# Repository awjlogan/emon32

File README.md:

# Energy Monitor 32

## Introduction

_Energy Monitor 32_ (emon32) is a system for measuring power consumption using _current transfomers_ (CTs). It is based heavily on the work done by [OpenEnergyMonitor](https://openenergymonitor.org), particularly the [emonTx](https://github.com/openenergymonitor/emontx4). It is designed to be compatible with the downstream data requirements of that system.

The emonTx energy monitors are currently based around the ATMega328, as made popular by Arduino, and an extended version, the AVR128DB. These chips are expensive, have few peripherals, and are being pushed to the limit of their data processing capability. The aims of this project are:

- Provide a low cost, high performance energy monitoring system.
- Provide a scalable and modular system.
- Provide an architecture agnostic library to handle energy monitoring functions.

There is also [firmware available](https://github.com/awjlogan/emon32-fw) to enable a complete energy monitoring system.

## Getting started

There is currently one implementation:

- [emonPi3](pcb/emonpi3/README.md)

> [!NOTE]
> The emonPi3 will be available full assembled from the OpenEnergyMonitor shop in 2025/2026.

## Microcontroller Selection

The firmware is agnostic to the microcontroller used, although a modern 32 bit core is preferred. This implementation targets the [Microchip SAMD series](https://www.microchip.com/en-us/products/microcontrollers-and-microprocessors/32-bit-mcus/sam-32-bit-mcus/sam-d) - this allows easy porting from small and cheap (SAMD1x) to higher performance and capability microcontrollers, such as the SAMD2x and SAMD5x. The SAMD family has the following useful functions

- Differential ADC (dual channel for SAMD5x)
- Asynchronous event system
  - This allows precise sample timing without any interrupt overhead
- Generic serial communication modules
- Flexible clocking system
  - High speed clocks are available for the core, and separate clocks for each peripheral
  - Clocks and peripherals can be gated when not in use
- USB virtual serial port (SAMD21 and SAMD51 only)
- USB bootloader (SAMD11, SAMD21, SAMD51 only)

If you would like to use a different microcontroller, the following features are recommended:

- Minimum 24 MHz clock
- Timer with 1 us resolution
- DMA (minimum 2 channels)
- 2x UART module
- SPI module
- I2C module

Functions in the main loop are abstacted from the underlying hardware. Implementation specific configuration (for example, configuring the ADC) must be provided.

## License

This project is licensed under the [Creative Commons Attribution Sharealike 4.0](https://creativecommons.org/licenses/by-sa/4.0/deed.en). Any alterations must be made available immediately, or upon request.

## Acknowledgements

- [OpenEnergyMonitor](https://openenergymonitor.org)
- Rob Wall of Open Energy Monitor forums for lots of in depth discussion around sampling strategies.
- Rupert on OEM forums for PCB improvements.

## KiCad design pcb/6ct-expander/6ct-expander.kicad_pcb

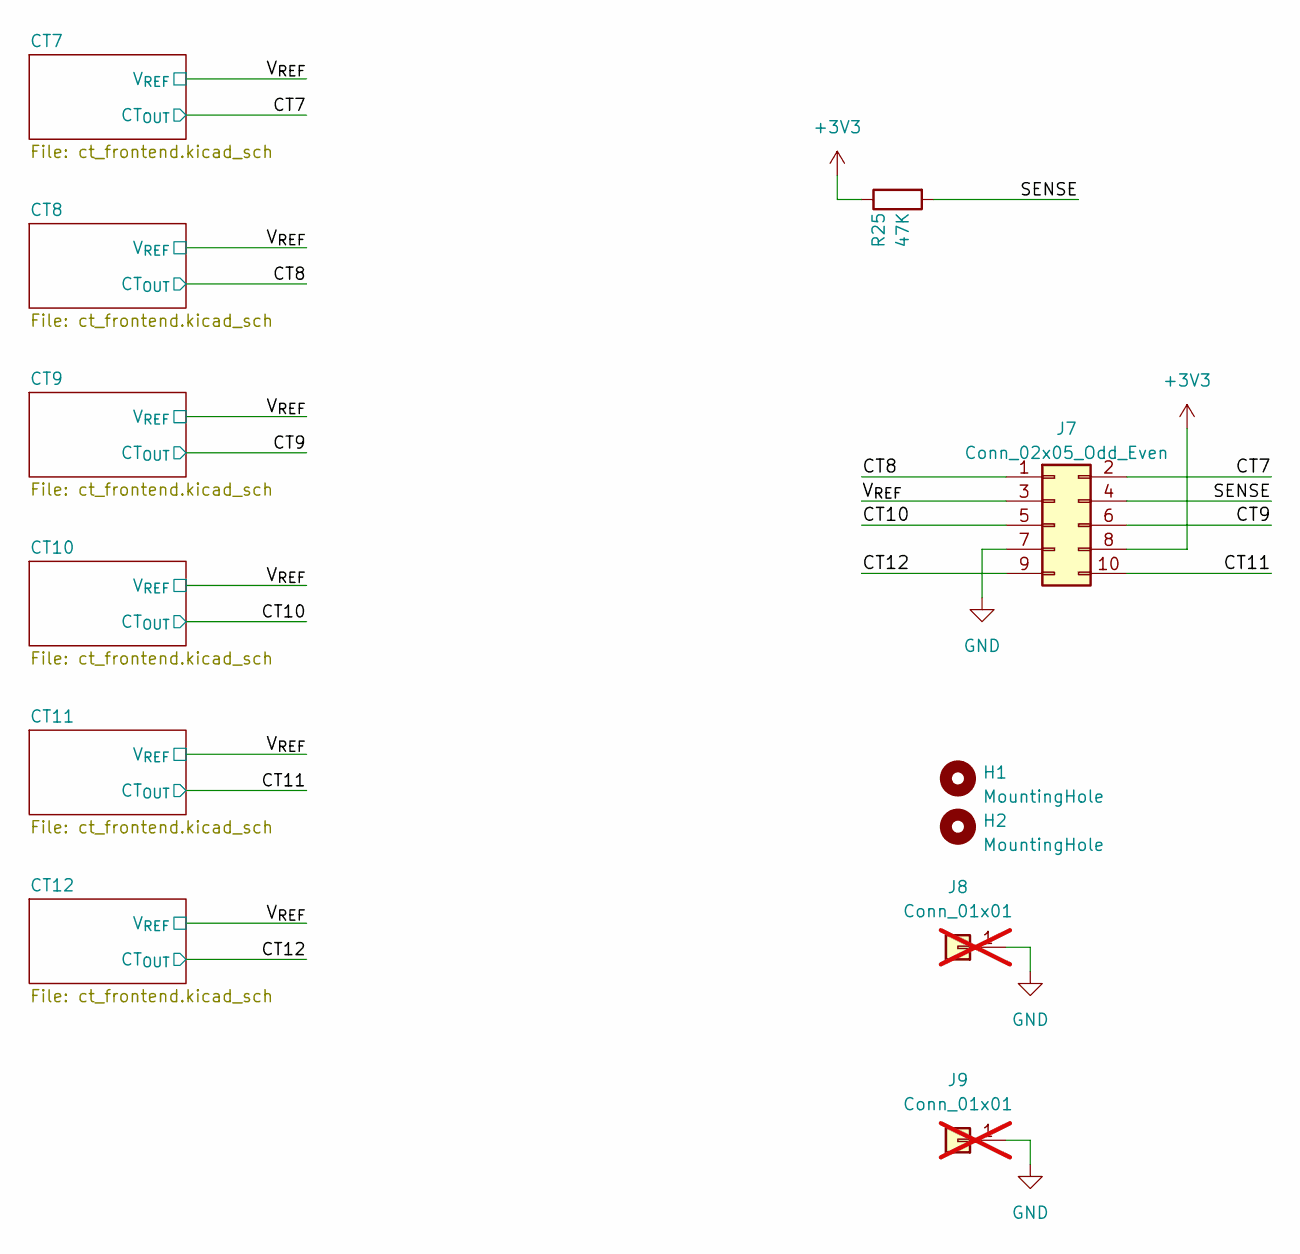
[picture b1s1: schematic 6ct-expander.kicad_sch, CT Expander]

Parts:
H1, H2: MountingHole; MountingHole_2.7mm_M2.5
J7: Conn_02x05_Odd_Even; PinHeader_2x05_P2.54mm_Vertical
J8, J9: Conn_01x01; PinHeader_1x01_P2.54mm_Vertical; not fitted
R25: 47K; R_0603_1608Metric; LCSC C23162

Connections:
+3V3: J7.8, R25.1
/CT7: J7.2; also elsewhere on the board
/CT8: J7.1; also elsewhere on the board
/CT9: J7.6; also elsewhere on the board
/CT10: J7.5; also elsewhere on the board
/CT11: J7.10; also elsewhere on the board
/CT12: J7.9; also elsewhere on the board
/SENSE: J7.4, R25.2
/V_{REF}: J7.3; also elsewhere on the board
GND: J7.7, J8.1, J9.1; also elsewhere on the board

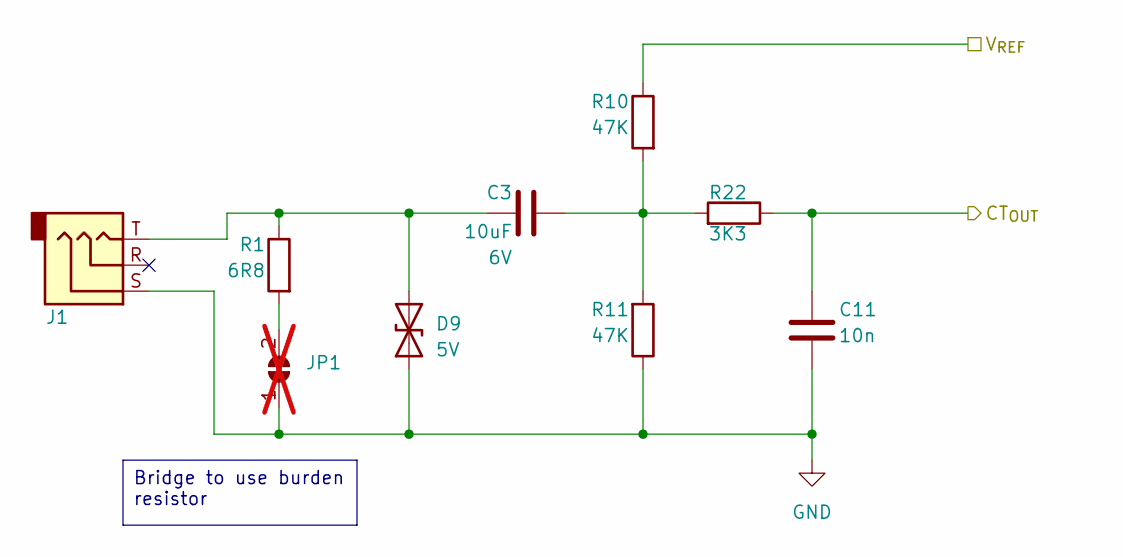
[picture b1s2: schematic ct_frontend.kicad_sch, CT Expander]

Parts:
C3: 10uF; C_0603_1608Metric; Voltage 6V; LCSC C19702
C11: 10n; C_0603_1608Metric; LCSC C57112
D9: 5V; D_SOD-523; MPN DF2B7AE,H3F; Mouser 757-DF2B7AEH3F
J1: SJ-3524-SMT-TR; Jack_3.5mm_CUI_SJ-3524-SMT_Horizontal; LCSC C4991872
JP1: SolderJumper_2_Open; SolderJumper-2_P1.3mm_Open_TrianglePad1.0x1.5mm; not fitted
R1: 6R8; R_1206_3216Metric; LCSC C2107438
R10, R11: 47K; R_0603_1608Metric; LCSC C23162
R22: 3K3; R_0603_1608Metric; LCSC C22978

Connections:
/CT7: C11.1, R22.1; also elsewhere on the board
/V_{REF}: R10.1; also elsewhere on the board
GND: C11.2, D9.1 (A1), J1.S, JP1.1 (A), R11.1; also elsewhere on the board
unnamed: C3.2, R10.2, R11.2, R22.2
unnamed: C3.1, D9.2 (A2), J1.T, R1.1
unnamed: JP1.2 (B), R1.2

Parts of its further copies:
C1, C4, C6, C8, C10: 10uF; C_0603_1608Metric; Voltage 6V; LCSC C19702
C2, C5, C7, C9, C12: 10n; C_0603_1608Metric; LCSC C57112
D1, D2, D3, D4, D5: 5V; D_SOD-523; MPN DF2B7AE,H3F; Mouser 757-DF2B7AEH3F
J2, J3, J4, J5, J6: SJ-3524-SMT-TR; Jack_3.5mm_CUI_SJ-3524-SMT_Horizontal; LCSC C4991872
JP2, JP3, JP4, JP5, JP6: SolderJumper_2_Open; SolderJumper-2_P1.3mm_Open_TrianglePad1.0x1.5mm; not fitted
R2, R6: 6R8; R_1206_3216Metric; LCSC C2107438
R3, R4, R7, R8, R13, R14, R17, R18, R21, R23: 47K; R_0603_1608Metric; LCSC C23162
R5, R9: 3K3; R_0603_1608Metric; LCSC C22978

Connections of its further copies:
/CT8: C2.1, R5.1; also elsewhere on the board
/CT9: C5.1, R9.1; also elsewhere on the board
/CT10: C7.1; also elsewhere on the board
/CT11: C9.1; also elsewhere on the board
/CT12: C12.1; also elsewhere on the board
/V_{REF}: R3.1, R7.1, R13.1, R17.1, R21.1; also elsewhere on the board
GND: C2.2, C5.2, C7.2, C9.2, C12.2, D1.1 (A1), D2.1 (A1), D3.1 (A1), D4.1 (A1), D5.1 (A1), J2.S, J3.S, J4.S, J5.S, J6.S, JP2.1 (A), JP3.1 (A), JP4.1 (A), JP5.1 (A), JP6.1 (A), R4.1, R8.1, R14.1, R18.1, R23.1; also elsewhere on the board
unnamed: C1.2, R3.2, R4.2, R5.2
unnamed: C4.2, R7.2, R8.2, R9.2
unnamed 13: C6.2, R13.2, R14.2; also elsewhere on the board
unnamed 14: C8.2, R17.2, R18.2; also elsewhere on the board
unnamed 15: C10.2, R21.2, R23.2; also elsewhere on the board
unnamed: C1.1, D1.2 (A2), J2.T, R2.1
unnamed: C4.1, D2.2 (A2), J3.T, R6.1
unnamed 18: C6.1, D3.2 (A2), J4.T; also elsewhere on the board
unnamed 19: C8.1, D4.2 (A2), J5.T; also elsewhere on the board
unnamed 20: C10.1, D5.2 (A2), J6.T; also elsewhere on the board
unnamed: JP2.2 (B), R2.2
unnamed: JP3.2 (B), R6.2
unnamed 25: JP4.2 (B); also elsewhere on the board
unnamed 26: JP5.2 (B); also elsewhere on the board
unnamed 27: JP6.2 (B); also elsewhere on the board

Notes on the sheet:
Bridge to use burden resistor

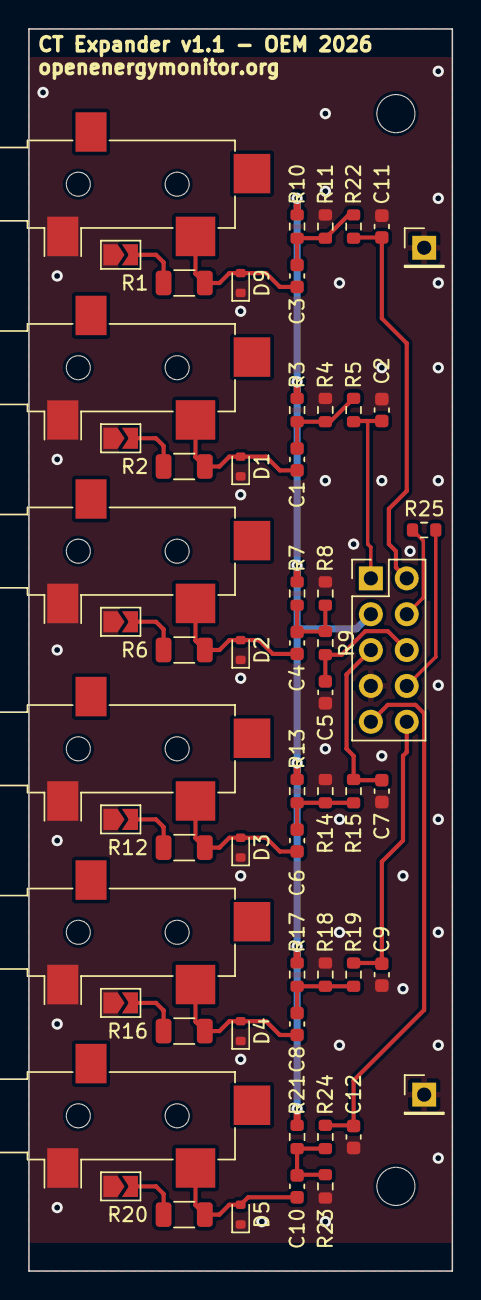
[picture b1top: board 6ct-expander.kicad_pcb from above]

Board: 2 copper layers, 30.0 x 88.0 mm, 60 parts (0 on the bottom side), 28 nets.

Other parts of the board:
R12, R16, R20: 6R8; R_1206_3216Metric
R15, R19, R24: 3K3; R_0603_1608Metric

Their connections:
/CT10: R15.1; also elsewhere on the board
/CT11: R19.1; also elsewhere on the board
/CT12: R24.1; also elsewhere on the board
unnamed 13: R15.2; also elsewhere on the board
unnamed 14: R19.2; also elsewhere on the board
unnamed 15: R24.2; also elsewhere on the board
unnamed 18: R12.1; also elsewhere on the board
unnamed 19: R16.1; also elsewhere on the board
unnamed 20: R20.1; also elsewhere on the board
unnamed 25: R12.2; also elsewhere on the board
unnamed 26: R16.2; also elsewhere on the board
unnamed 27: R20.2; also elsewhere on the board

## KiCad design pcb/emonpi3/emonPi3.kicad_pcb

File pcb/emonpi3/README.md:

# emonPi3

_emonPi3_ is a drop in replacement for the [emonPi2](https://docs.openenergymonitor.org/emonpi2/index.html). The main change is the use of a modern high performance microcontroller in place of the aging and expensive AVR parts. Additionally, the firmware moves away from using Arduino as the base environment.

## Firmware

Firmware for the emonPi3 is available [here](https://github.com/awjlogan/emon32-fw). The emonPi3 comes preloaded with a USB bootloader, allowing the firmware to be updated without any specialised hardware.

## Generating manufacturing outputs

You will need to have [KiCad 7](https://www.kicad.org/) installed. In the `emonpi3` folder, run `python3 generate.py`. This will make a folder called `output-<gitrev>` with the following contents:

  - KiCad schematic annotated with git revision
  - KiCad PCB annotated with git revision
  - Schematic PDF
  - Floorplan PDF
  - Bill of materials CSV
  - Gerbers output
  - 3D render (STEP format)

This has been tested on Linux and macOS.

## Changelog

### 1.0

Production

- Correct front panel LED footprint
- Routing tweaks

### 0.2

First production candidate

- Correct SPI connection
- Move LED to front panel
- ESD protection on all inputs and buttons
- Expose reset to Pi connection

### 0.1

First public limited manufacturing run.

- Add hardware zero crossing detector.
- Add ADC calibration hardware.
- Add more testpoints.
- Move EEPROM and reassign serial modules.
- Add user button, LEDs, and external I2C header.

### 0.1-dev

- First bring up of the emonPi3. 
  - Directly physically compatible with the existing emonPi2. 
- Change to 4-layer board
- Add extra filters and power protection

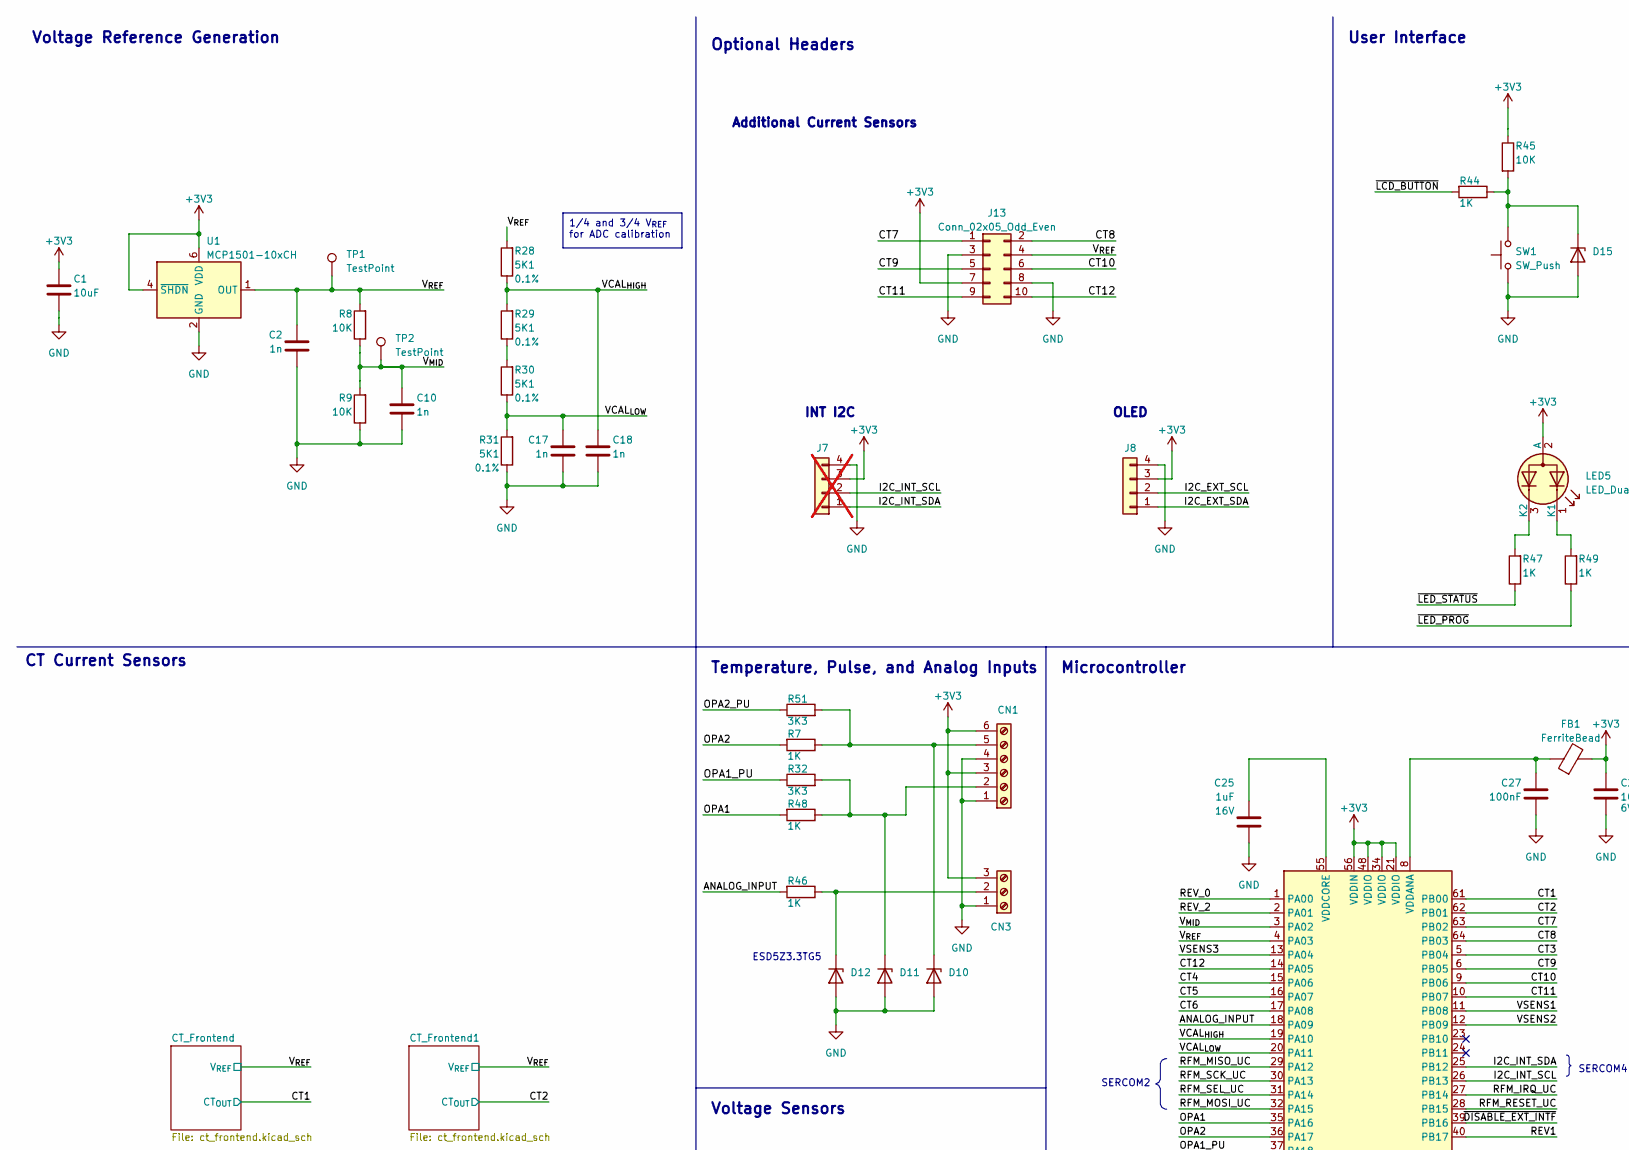
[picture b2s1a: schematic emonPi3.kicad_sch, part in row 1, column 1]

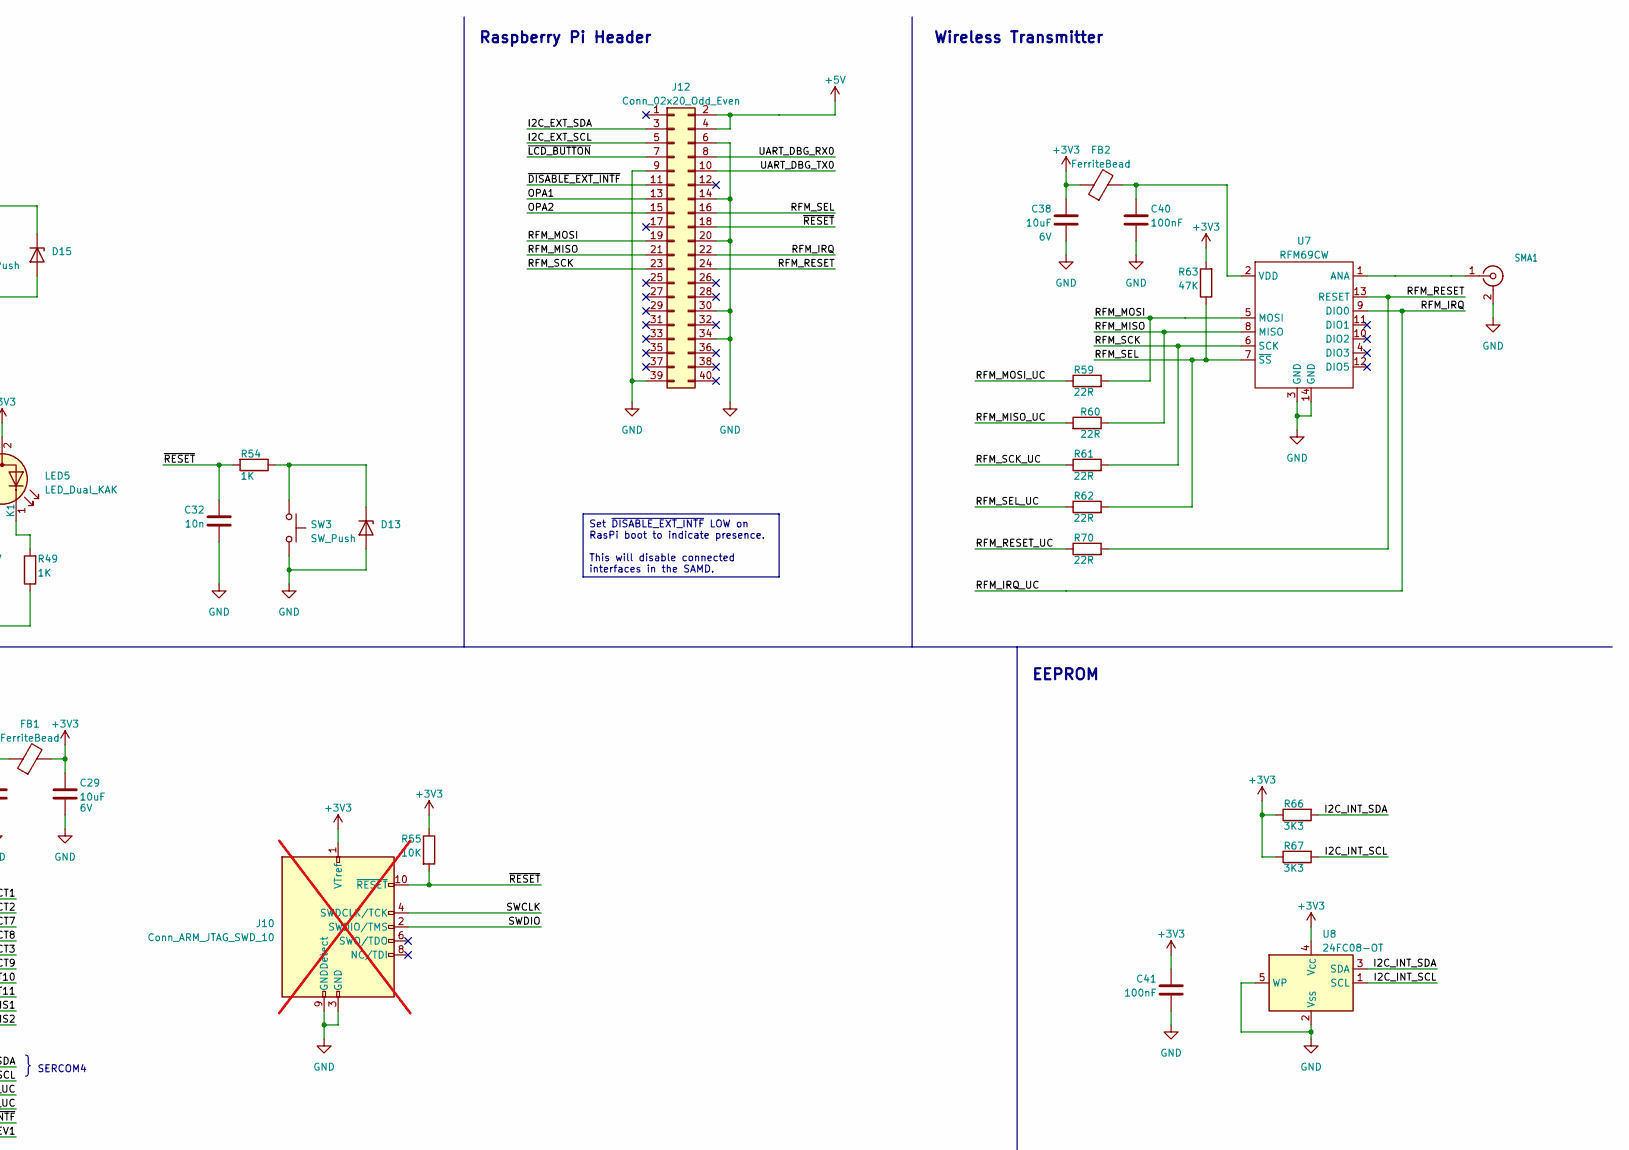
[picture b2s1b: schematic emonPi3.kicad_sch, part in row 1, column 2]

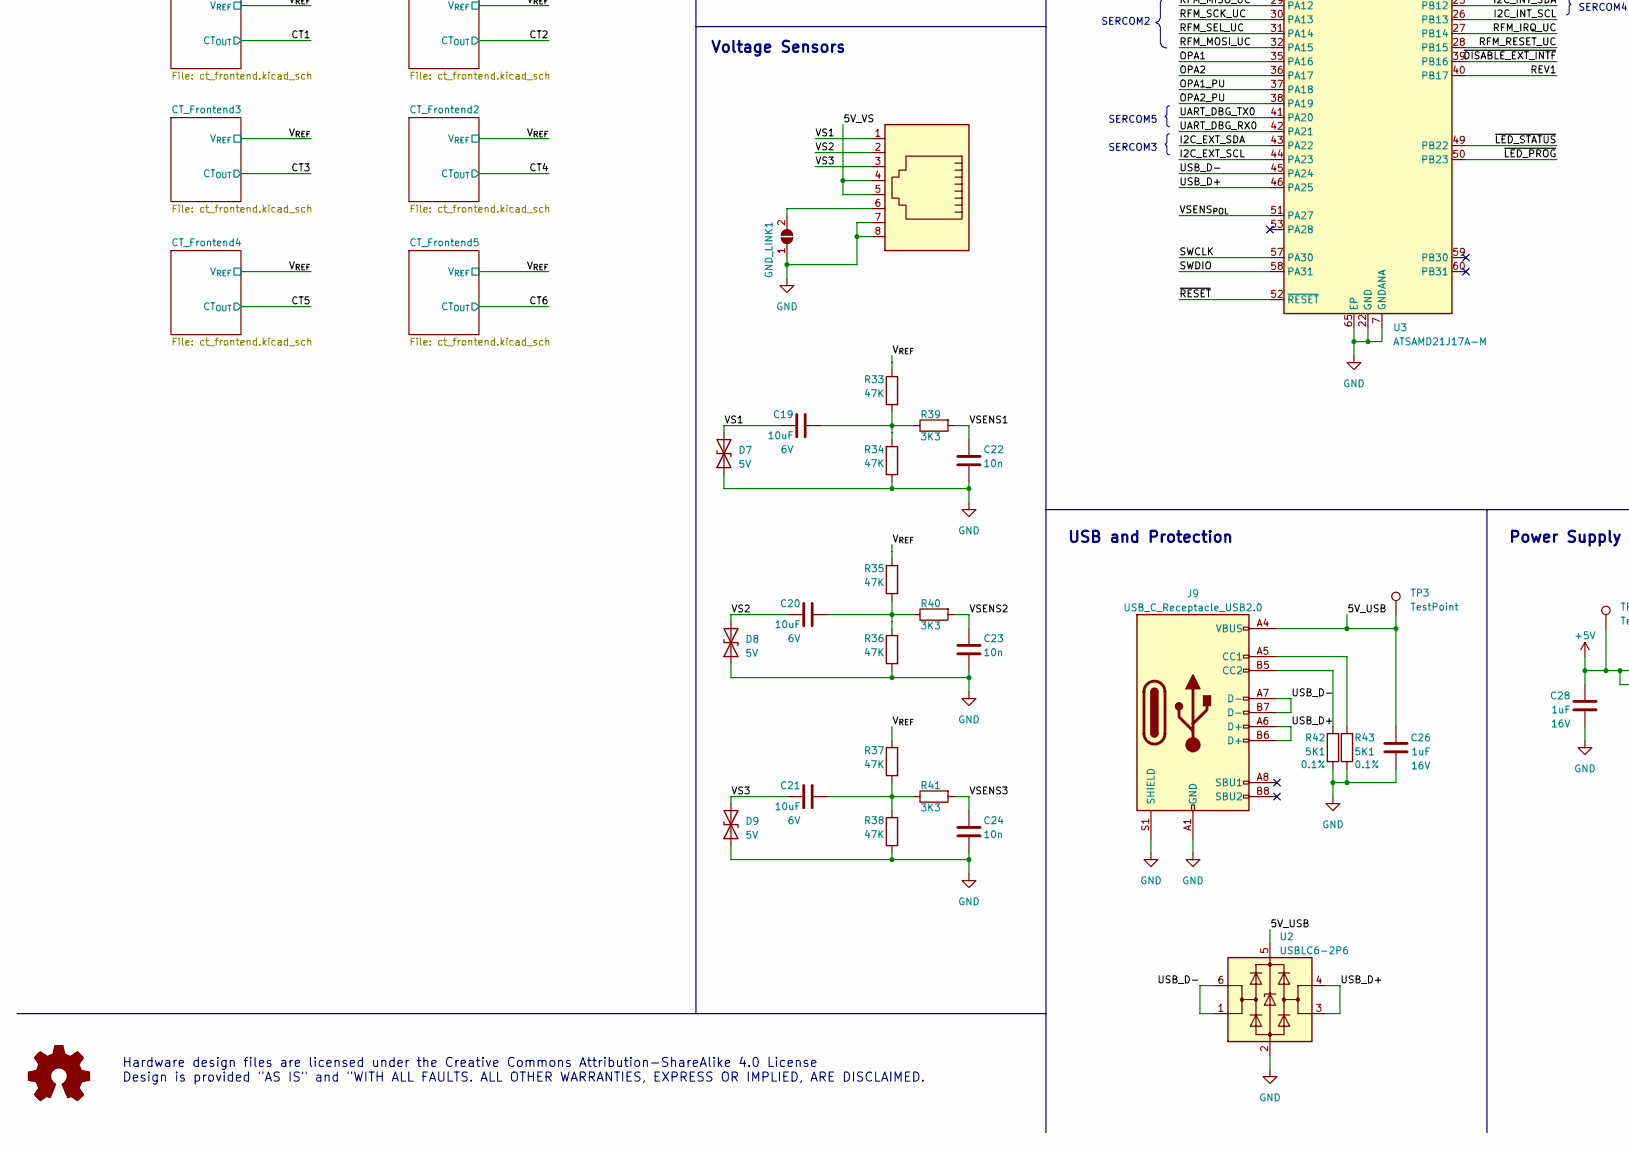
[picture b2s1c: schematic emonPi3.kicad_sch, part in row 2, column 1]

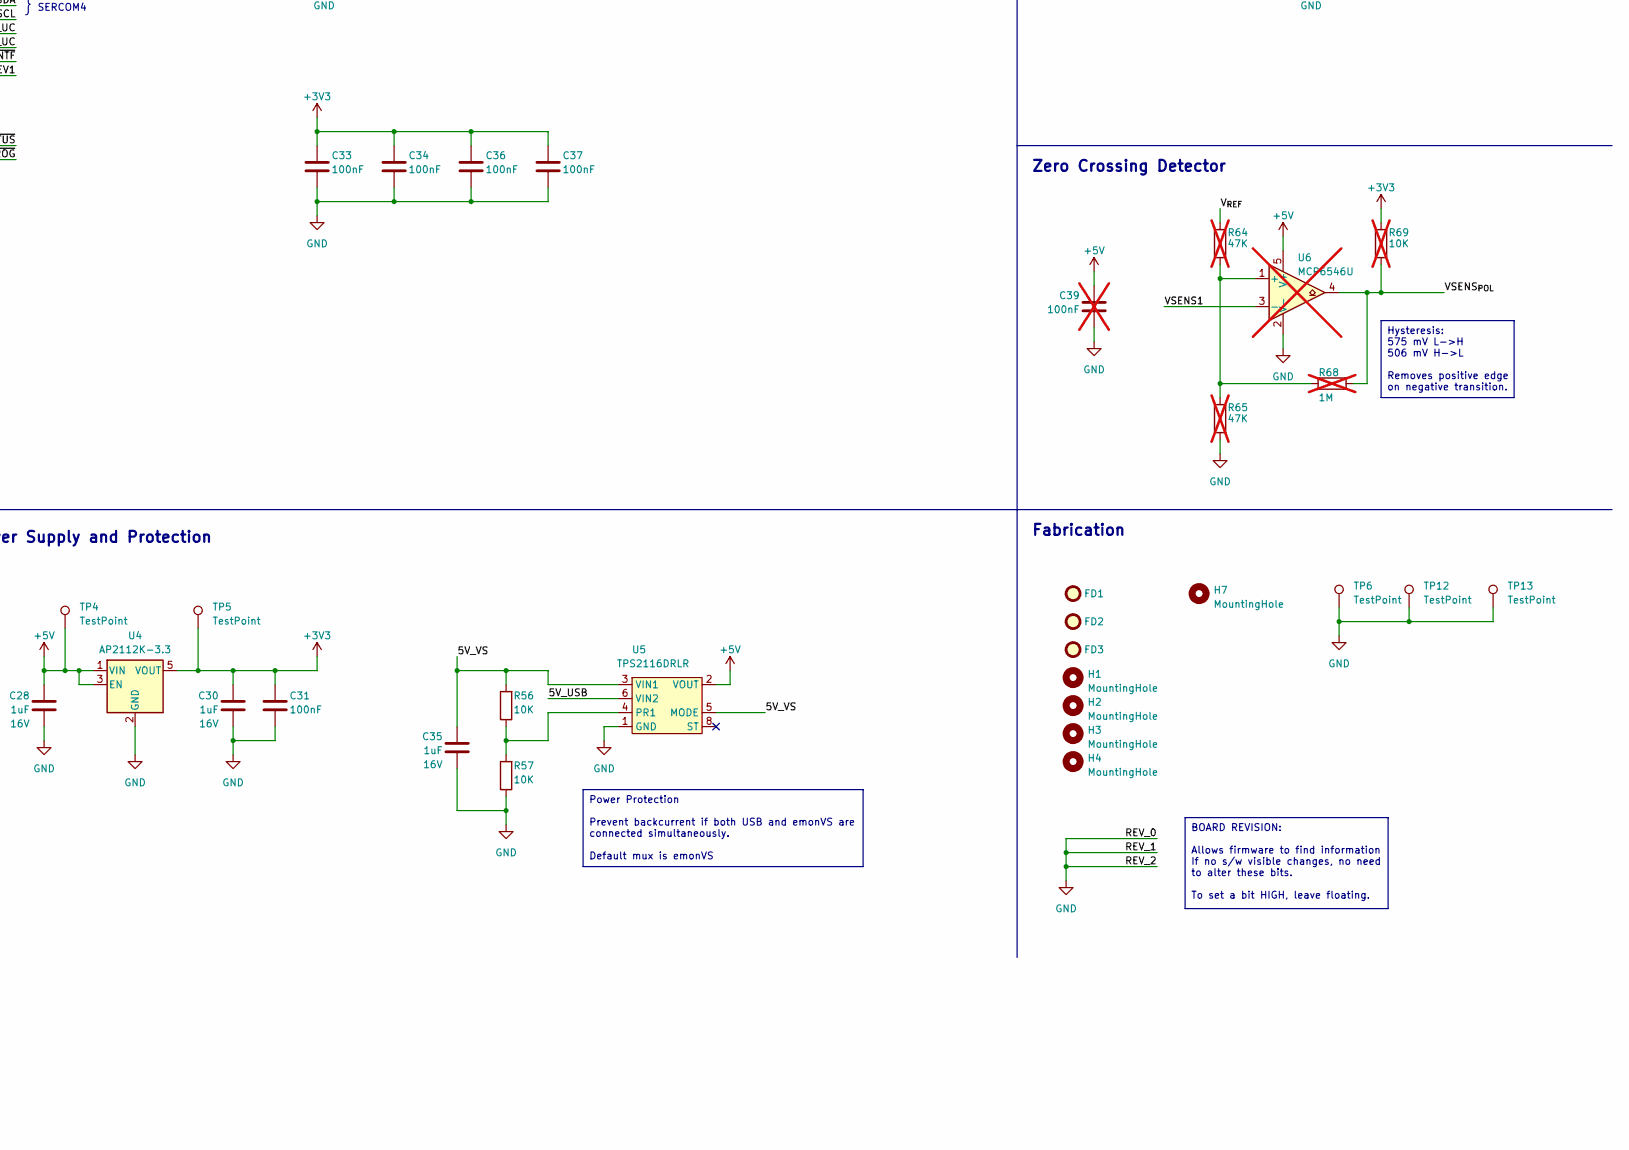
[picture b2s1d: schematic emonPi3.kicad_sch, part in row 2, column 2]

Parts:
C1: 10uF; C_0603_1608Metric
C2, C10, C17, C18: 1n; C_0603_1608Metric
C19, C20, C21, C29, C38: 10uF; C_0603_1608Metric; Voltage 6V
C22, C23, C24, C32: 10n; C_0603_1608Metric
C25, C26, C28, C30, C35: 1uF; C_0603_1608Metric; Voltage 16V
C27, C31, C33, C34, C36, C37, C40, C41: 100nF; C_0603_1608Metric
C39: 100nF; C_0603_1608Metric; not fitted
CN1: Screw_Terminal_01x06; TerminalBlock_Phoenix_PT-1,5-6-3.5-H_1x06_P3.50mm_Horizontal
CN3: CONN_03SCREW; TerminalBlock_Phoenix_PT-1,5-3-3.5-H_1x03_P3.50mm_Horizontal
D7, D8, D9: 5V; D_SOD-523; MPN DF2B7AE,H3F; Mouser 757-DF2B7AEH3F
D10, D11, D12, D13, D15: ESD5Z3.3T5G; D_SOD-523
FB1: FerriteBead; R_0603_1608Metric; MPN MPZ1608D300BTA00
FB2: FerriteBead; R_0603_1608Metric
FD1, FD2, FD3: FIDUCIAL1X2; Fiducial_0.75mm_Mask1.5mm
GND_LINK1: SOLDERJUMPERNC; SolderJumper-2_P1.3mm_Open_TrianglePad1.0x1.5mm
H1, H2, H3, H4: MountingHole; MountingHole_2.7mm_M2.5
H7: MountingHole; MountingHole_2.1mm
J7: CONN_04PTH; PinSocket_1x04_P2.54mm_Vertical; not fitted
J8: CONN_04PTH; PinSocket_1x04_P2.54mm_Vertical
J9: USB_C_Receptacle_USB2.0; CSP-USC16-TR
J10: Conn_ARM_JTAG_SWD_10; PinHeader_2x05_P1.27mm_Vertical_SMD; not fitted
J12: Conn_02x20_Odd_Even; REF-182665
J13: Conn_02x05_Odd_Even; PinSocket_2x05_P2.54mm_Vertical
LED5: LED_Dual_KAK; LED_LiteOn_LTST-S326; MPN LTST-S326KGJRKT; Mouser 859-LTST-S326KGJRKT
R7, R44, R46, R47, R48, R49, R54: 1K; R_0603_1608Metric
R8, R9, R45, R55, R56, R57: 10K; R_0603_1608Metric
R28, R29, R30, R31: 5K1; R_0603_1608Metric; Tolerance 0.1%
R32, R39, R40, R41, R51, R66, R67: 3K3; R_0603_1608Metric
R33, R34, R35, R36, R37, R38, R63: 47K; R_0603_1608Metric
R42, R43: 5K1; R_0603_1608Metric; Tolerance 0.1%; MPN ERA-3AED512V; Mouser 667-ERA-3AED512V
R59, R60, R61, R62, R70: 22R; R_0603_1608Metric
R64, R65: 47K; R_0603_1608Metric; not fitted
R68: 1M; R_0603_1608Metric; not fitted
R69: 10K; R_0603_1608Metric; not fitted
RJ1: RJ45-8PTH; RJ45_Amphenol_54602-x08_Horizontal; MPN 54602-908LF; Mouser 649-54602-908LF
SMA1: SMACONNECTOR; SMA_Amphenol_132203-12_Horizontal
SW1: SW_Push; SW_PUSH_6mm
SW3: SW_Push; SW_Tactile_SPST_NO_Straight_CK_PTS636Sx25SMTRLFS
TP1, TP2, TP3, TP4, TP5, TP6, TP12, TP13: TestPoint; TestPoint_Pad_D1.0mm
U1: MCP1501-10xCH; SOT-23-6; MPN MCP1501T-10E/CHY; Mouser 579-MCP1501T-10E/CHY
U2: USBLC6-2P6; SOT-666; MPN USBLC6-2P6; Mouser 511-USBLC6-2P6
U3: ATSAMD21J17A-M; QFN-64-1EP_9x9mm_P0.5mm_EP4.7x4.7mm; MPN ATSAMD21J17A-MU; Mouser 556-ATSAMD21J17A-MU
U4: AP2112K-3.3; SOT-23-5; MPN AP2112K-3.3TRG1; Mouser 621-AP2112K-3.3TRG1
U5: TPS2116DRLR; SOT-583-8; MPN TPS2116DRLR; Mouser 595-TPS2116DRLR
U6: MCP6546U; SOT-23-5; MPN MCP6546U-E/OT; Mouser 579-MCP6546UT-E/OT; not fitted
U7: RFM69CW
U8: 24FC08-OT; SOT-23-5; MPN 24FC08T-I/OT; Mouser 579-24FC08T-I/OT

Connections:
+3V3: C1.1, C29.1, C30.2, C31.2, C33.1, C34.1, C36.1, C37.1, C38.1, C41.1, CN1.3, CN1.6, CN3.3, FB1.2, FB2.1, J7.3, J8.3, J10.1 (VTref), J13.7, LED5.2 (A), R45.1, R55.1, R63.2, R66.1, R67.1, R69.1, TP5.1, U1.4 (~SHDN), U1.6 (VDD), U3.21 (VDDIO), U3.34 (VDDIO), U3.48 (VDDIO), U3.56 (VDDIN), U4.5 (VOUT), U8.4 (V_{CC})
+5V: C28.2, C39.1, J12.2, J12.4, TP4.1, U4.1 (VIN), U4.3 (EN), U5.2 (VOUT), U5.7 (VOUT), U6.5 (V+)
/5V_USB: C26.2, J9.A4 (VBUS), J9.A9 (VBUS), J9.B4 (VBUS), J9.B9 (VBUS), TP3.1, U2.5 (VBUS), U5.6 (VIN2)
/5V_VS: C35.2, R56.2, RJ1.4, RJ1.5, U5.3 (VIN1), U5.5 (MODE)
/ANALOG_INPUT: R46.2, U3.18 (PA09)
/CT1: U3.61 (PB00); also elsewhere on the board
/CT2: U3.62 (PB01); also elsewhere on the board
/CT3: U3.5 (PB04); also elsewhere on the board
/CT4: U3.15 (PA06); also elsewhere on the board
/CT5: U3.16 (PA07); also elsewhere on the board
/CT6: U3.17 (PA08); also elsewhere on the board
/CT7: J13.1, U3.63 (PB02)
/CT8: J13.2, U3.64 (PB03)
/CT9: J13.5, U3.6 (PB05)
/CT10: J13.6, U3.9 (PB06)
/CT11: J13.9, U3.10 (PB07)
/CT12: J13.10, U3.14 (PA05)
/I2C_EXT_SCL: J8.2, J12.5, U3.44 (PA23)
/I2C_EXT_SDA: J8.1, J12.3, U3.43 (PA22)
/I2C_INT_SCL: J7.2, R67.2, U3.26 (PB13), U8.1 (SCL)
/I2C_INT_SDA: J7.1, R66.2, U3.25 (PB12), U8.3 (SDA)
/OPA1: J12.13, R48.2, U3.35 (PA16)
/OPA1_PU: R32.1, U3.37 (PA18)
/OPA2: J12.15, R7.2, U3.36 (PA17)
/OPA2_PU: R51.1, U3.38 (PA19)
/REV1: U3.40 (PB17)
/RFM_IRQ: J12.22, U3.27 (PB14), U7.9 (DIO0)
/RFM_MISO: J12.21, R60.1, U7.8 (MISO)
/RFM_MISO_UC: R60.2, U3.29 (PA12)
/RFM_MOSI: J12.19, R59.2, U7.5 (MOSI)
/RFM_MOSI_UC: R59.1, U3.32 (PA15)
/RFM_RESET: J12.24, R70.2, U7.13 (RESET)
/RFM_RESET_UC: R70.1, U3.28 (PB15)
/RFM_SCK: J12.23, R61.2, U7.6 (SCK)
/RFM_SCK_UC: R61.1, U3.30 (PA13)
/RFM_SEL: J12.16, R62.2, R63.1, U7.7 (~SS)
/RFM_SEL_UC: R62.1, U3.31 (PA14)
/SWCLK: J10.4 (SWDCLK/TCK), U3.57 (PA30)
/SWDIO: J10.2 (SWDIO/TMS), U3.58 (PA31)
/UART_DBG_RX0: J12.8, U3.42 (PA21)
/UART_DBG_TX0: J12.10, U3.41 (PA20)
/USB_D+: J9.A6 (D+), J9.B6 (D+), U2.3 (I/O2), U2.4 (I/O2), U3.46 (PA25)
/USB_D-: J9.A7 (D-), J9.B7 (D-), U2.1 (I/O1), U2.6 (I/O1), U3.45 (PA24)
/VCAL_{HIGH}: C18.1, R28.1, R29.2, U3.19 (PA10)
/VCAL_{LOW}: C17.1, R30.1, R31.2, U3.20 (PA11)
/VS1: C19.1, D7.2 (A2), RJ1.1
/VS2: C20.1, D8.2 (A2), RJ1.2
/VSENS1: C22.1, R39.2, U3.11 (PB08), U6.3 (-)
/VSENS2: C23.1, R40.2, U3.12 (PB09)
/VSENS3: C24.1, R41.2, U3.13 (PA04)
/VSENS_{POL}: R68.2, R69.2, U3.51 (PA27), U6.4
/V_{MID}: C10.1, R8.1, R9.2, TP2.1, U3.3 (PA02)
/V_{REF}: C2.1, J13.4, R8.2, R28.2, R33.1, R35.1, R37.1, R64.1, TP1.1, U1.1 (OUT), U3.4 (PA03); also elsewhere on the board
/~DISABLE_EXT_INTF: J12.11, U3.39 (PB16)
/~LCD_BUTTON: J12.7, R44.2
/~LED_PROG: R49.1, U3.50 (PB23)
/~LED_STATUS: R47.1, U3.49 (PB22)
/~RESET: C32.1, J10.10 (~RESET), J12.18, R54.2, R55.2, U3.52 (~RESET)
GND: C1.2, C2.2, C10.2, C17.2, C18.2, C22.2, C23.2, C24.2, C25.2, C26.1, C27.2, C28.1, C29.2, C30.1, C31.1, C32.2, C33.2, C34.2, C35.1, C36.2, C37.2, C38.2, C39.2, C40.2, C41.2, CN1.1, CN1.4, CN3.1, D7.1 (A1), D8.1 (A1), D9.1 (A1), D10.2 (A), D11.2 (A), D12.2 (A), D13.2 (A), D15.2 (A), GND_LINK1.1 (A), J7.4, J8.4, J9.A1 (GND), J9.A12 (GND), J9.B1 (GND), J9.B12 (GND), J9.S1 (SHIELD), J10.3 (GND), J10.5 (GND), J10.9 (GNDDetect), J12.6, J12.9, J12.14, J12.20, J12.30, J12.34, J12.39, J13.3, J13.8, R9.1, R31.1, R34.1, R36.2, R38.2, R42.1, R43.1, R57.1, R65.2, RJ1.7, RJ1.8, SMA1.2 (Ext), SW1.1, SW3.2, TP6.1, TP12.1, TP13.1, U1.2 (GND), U1.3 (GND), U1.5 (GND), U2.2 (GND), U3.1 (PA00), U3.2 (PA01), U3.7 (GNDANA), U3.22 (GND), U3.33 (GND), U3.47 (GND), U3.54 (GND), U3.65 (EP), U4.2 (GND), U5.1 (GND), U6.2 (V-), U7.3 (GND), U7.14 (GND), U8.2 (V_{SS}), U8.5 (WP); also elsewhere on the board
unnamed: C19.2, R33.2, R34.2, R39.1
unnamed: C20.2, R35.2, R36.1, R40.1
unnamed: C21.2, R37.2, R38.1, R41.1
unnamed: CN1.2, D11.1 (K), R32.2, R48.1
unnamed: CN1.5, D10.1 (K), R7.1, R51.2
unnamed: CN3.2, D12.1 (K), R46.1
unnamed: D13.1 (K), R54.1, SW3.1
unnamed: D15.1 (K), R44.1, R45.2, SW1.2
unnamed: GND_LINK1.2 (B), RJ1.6
unnamed: J9.A5 (CC1), R43.2
unnamed: J9.B5 (CC2), R42.2
unnamed: LED5.1 (K1), R49.2
unnamed: LED5.3 (K2), R47.2
unnamed: R29.1, R30.2
unnamed: SMA1.1 (In), U7.1 (ANA)
unnamed: C27.1, FB1.1, U3.8 (VDDANA)
unnamed: C25.1, U3.55 (VDDCORE)
unnamed: R56.1, R57.2, U5.4 (PR1)
unnamed: R64.2, R65.1, R68.1, U6.1 (+)
unnamed: C40.1, FB2.2, U7.2 (VDD)

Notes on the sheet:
Power Protection Prevent backcurrent if both USB and emonVS are connected simultaneously. Default mux is emonVS
Set ~{DISABLE_EXT_INTF} LOW on RasPi boot to indicate presence. This will disable connected interfaces in the SAMD.
Hysteresis: 575 mV L->H 506 mV H->L Removes positive edge on negative transition.
BOARD REVISION: Allows firmware to find information If no s/w visible changes, no need to alter these bits. To set a bit HIGH, leave floating.
1/4 and 3/4 V_{REF} for ADC calibration
Raspberry Pi Header
Power Supply and Protection
Temperature, Pulse, and Analog Inputs
Hardware design files are licensed under the Creative Commons Attribution-ShareAlike 4.0 License Design is provided "AS IS" and "WITH ALL FAULTS. ALL OTHER WARRANTIES, EXPRESS OR IMPLIED, ARE DISCLAIMED.
Microcontroller
ESD5Z3.3TG5
Zero Crossing Detector
User Interface
SERCOM5
Voltage Reference Generation
Additional Current Sensors
SERCOM3
USB and Protection
EEPROM
INT I2C
Fabrication
OLED
SERCOM4
Voltage Sensors
CT Current Sensors
SERCOM2
Optional Headers
Wireless Transmitter

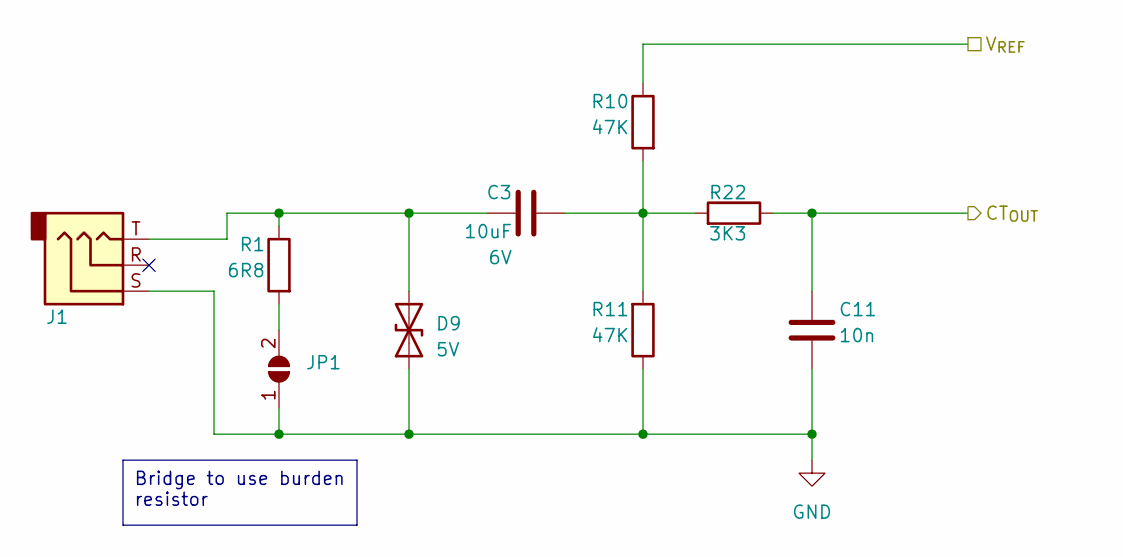
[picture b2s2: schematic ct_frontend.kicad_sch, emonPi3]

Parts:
C3: 10uF; C_0603_1608Metric; Voltage 6V
C11: 10n; C_0603_1608Metric
D9: 5V; D_SOD-523; MPN DF2B7AE,H3F; Mouser 757-DF2B7AEH3F
J1: SJ-3524-SMT-TR; Jack_3.5mm_CUI_SJ-3524-SMT_Horizontal
JP1: SolderJumper_2_Open; SolderJumper-2_P1.3mm_Open_TrianglePad1.0x1.5mm
R1: 6R8; R_1206_3216Metric
R10, R11: 47K; R_0603_1608Metric
R22: 3K3; R_0603_1608Metric

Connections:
/CT1: C11.1, R22.1; also elsewhere on the board
/V_{REF}: R10.1; also elsewhere on the board
GND: C11.2, D9.1 (A1), J1.S, JP1.1 (A), R11.1; also elsewhere on the board
unnamed: C3.2, R10.2, R11.2, R22.2
unnamed: JP1.2 (B), R1.2

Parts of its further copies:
C4, C6, C8, C13, C15: 10uF; C_0603_1608Metric; Voltage 6V
C5, C7, C12, C14, C16: 10n; C_0603_1608Metric
D1, D2, D3, D4, D5, D6: 5V; D_SOD-523; MPN DF2B7AE,H3F; Mouser 757-DF2B7AEH3F
J2, J3, J4, J5, J6: SJ-3524-SMT-TR; Jack_3.5mm_CUI_SJ-3524-SMT_Horizontal
JP2, JP3, JP4, JP5, JP6: SolderJumper_2_Open; SolderJumper-2_P1.3mm_Open_TrianglePad1.0x1.5mm
R2, R6, R15, R19, R24: 6R8; R_1206_3216Metric
R3, R4, R12, R13, R16, R17, R20, R21, R25, R26: 47K; R_0603_1608Metric
R5, R14, R18, R23, R27: 3K3; R_0603_1608Metric

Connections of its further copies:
/CT2: C5.1, R5.1; also elsewhere on the board
/CT3: C7.1, R14.1; also elsewhere on the board
/CT4: C12.1, R18.1; also elsewhere on the board
/CT5: C14.1, R23.1; also elsewhere on the board
/CT6: C16.1, R27.1; also elsewhere on the board
/V_{REF}: R3.1, R12.1, R16.1, R20.1, R25.1; also elsewhere on the board
GND: C5.2, C7.2, C12.2, C14.2, C16.2, D1.1 (A1), D2.1 (A1), D3.1 (A1), D4.1 (A1), D5.1 (A1), D6.1 (A1), J2.S, J3.S, J4.S, J5.S, J6.S, JP2.1 (A), JP3.1 (A), JP4.1 (A), JP5.1 (A), JP6.1 (A), R4.1, R13.1, R17.1, R21.1, R26.1; also elsewhere on the board
unnamed: C4.2, R3.2, R4.2, R5.2
unnamed: C6.2, R12.2, R13.2, R14.2
unnamed: C8.2, R16.2, R17.2, R18.2
unnamed: C13.2, R20.2, R21.2, R23.2
unnamed: C15.2, R25.2, R26.2, R27.2
unnamed: C4.1, D2.2 (A2), J2.T, R2.1
unnamed: C6.1, D3.2 (A2), J3.T, R6.1
unnamed: C8.1, D4.2 (A2), J4.T, R15.1
unnamed: C13.1, D5.2 (A2), J5.T, R19.1
unnamed: C15.1, D6.2 (A2), J6.T, R24.1
unnamed: JP2.2 (B), R2.2
unnamed: JP3.2 (B), R6.2
unnamed: JP4.2 (B), R15.2
unnamed: JP5.2 (B), R19.2
unnamed: JP6.2 (B), R24.2

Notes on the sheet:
Bridge to use burden resistor

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
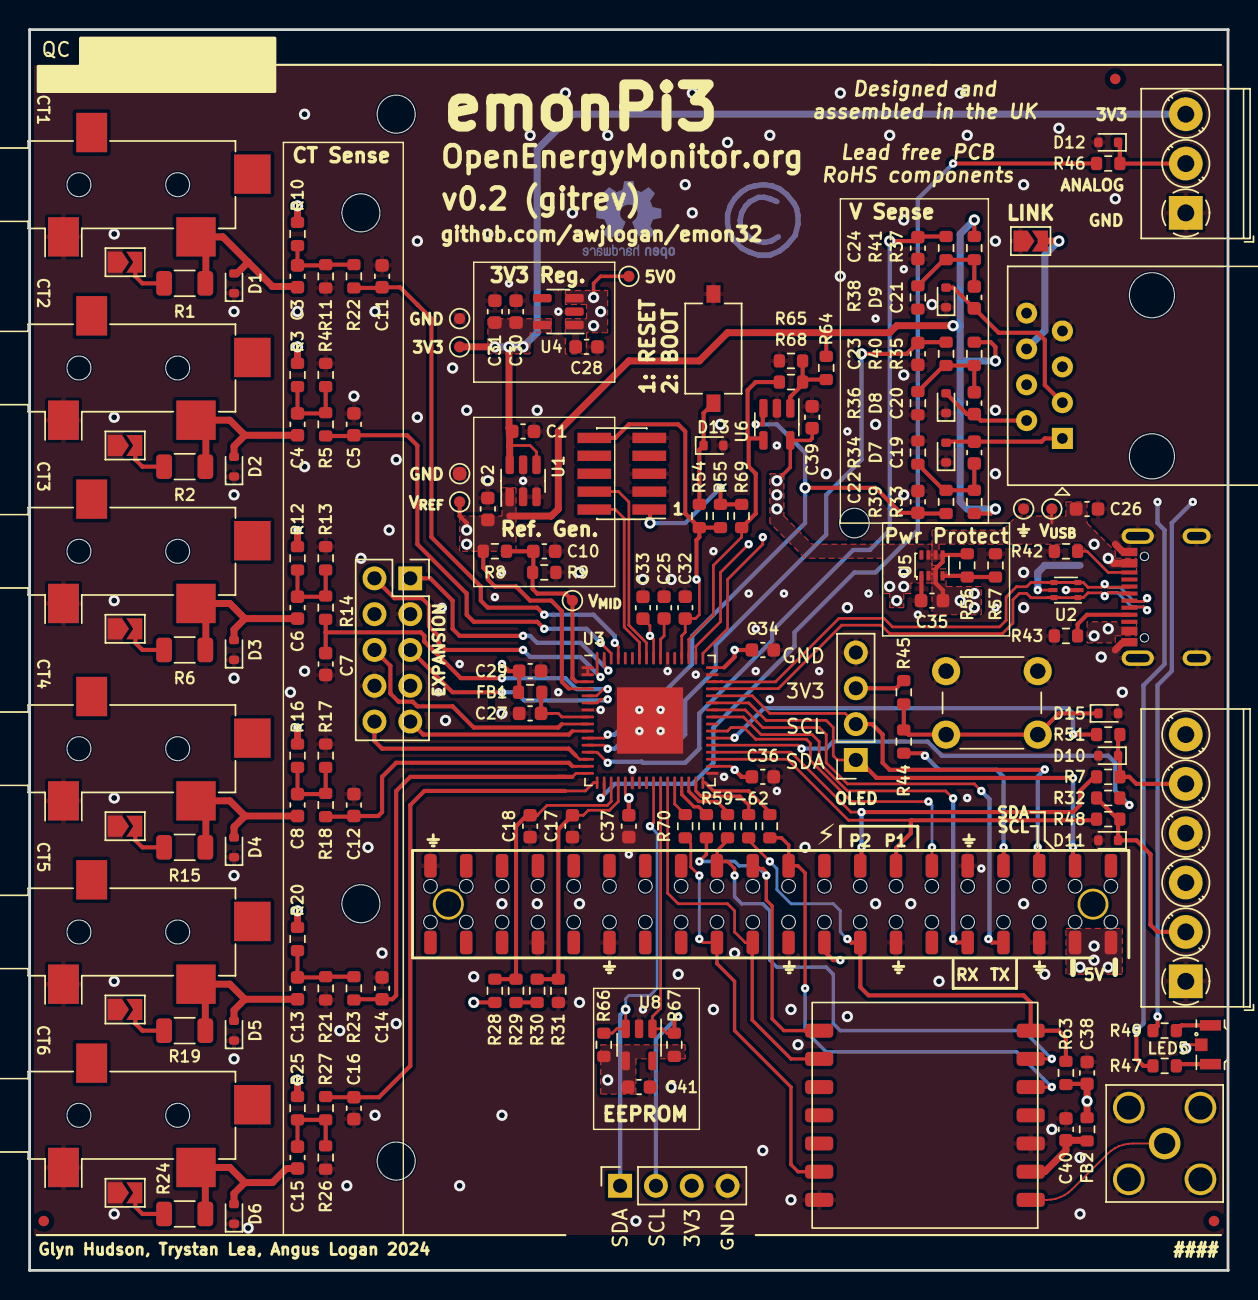
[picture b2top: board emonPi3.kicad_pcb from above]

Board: 4 copper layers, 85.0 x 88.0 mm, 172 parts (0 on the bottom side), 97 nets.
